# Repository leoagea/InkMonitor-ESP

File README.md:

# InkMonitor-ESP

InkMonitor-ESP is a lightweight temperature and humidity monitoring device built around an ESP microcontroller and an e‑paper display. This repository contains the hardware design files (KiCad) for the PCB and supporting assets.

## Highlights

- Low‑power ESP‑based monitoring platform
- E‑paper display for always‑on status with minimal power draw
- KiCad project files, BOM export, and board backups included

## Repository contents

- [PCB/](PCB/) — KiCad project, board/schematic, BOM, CAD assets, and exports
- [changelog.md](changelog.md) — project changes

## Hardware overview

The design targets a compact ESP‑based module (ESP32‑S3 class) paired with a temperature/humidity sensor and a small e‑paper display. The exact parts and footprints are defined in the KiCad files.

If you want to review or edit the design, open the KiCad project file:

- [PCB/InkMonitor-ESP.kicad_pro](PCB/InkMonitor-ESP.kicad_pro)

## Renders

1. Open the project file: [PCB/InkMonitor-ESP.kicad_pro](PCB/InkMonitor-ESP.kicad_pro).
2. Review the schematic: [PCB/InkMonitor-ESP.kicad_sch](PCB/InkMonitor-ESP.kicad_sch).
3. Review the PCB layout: [PCB/InkMonitor-ESP.kicad_pcb](PCB/InkMonitor-ESP.kicad_pcb).

## Firmware

WIP

## License

See [LICENSE](LICENSE).

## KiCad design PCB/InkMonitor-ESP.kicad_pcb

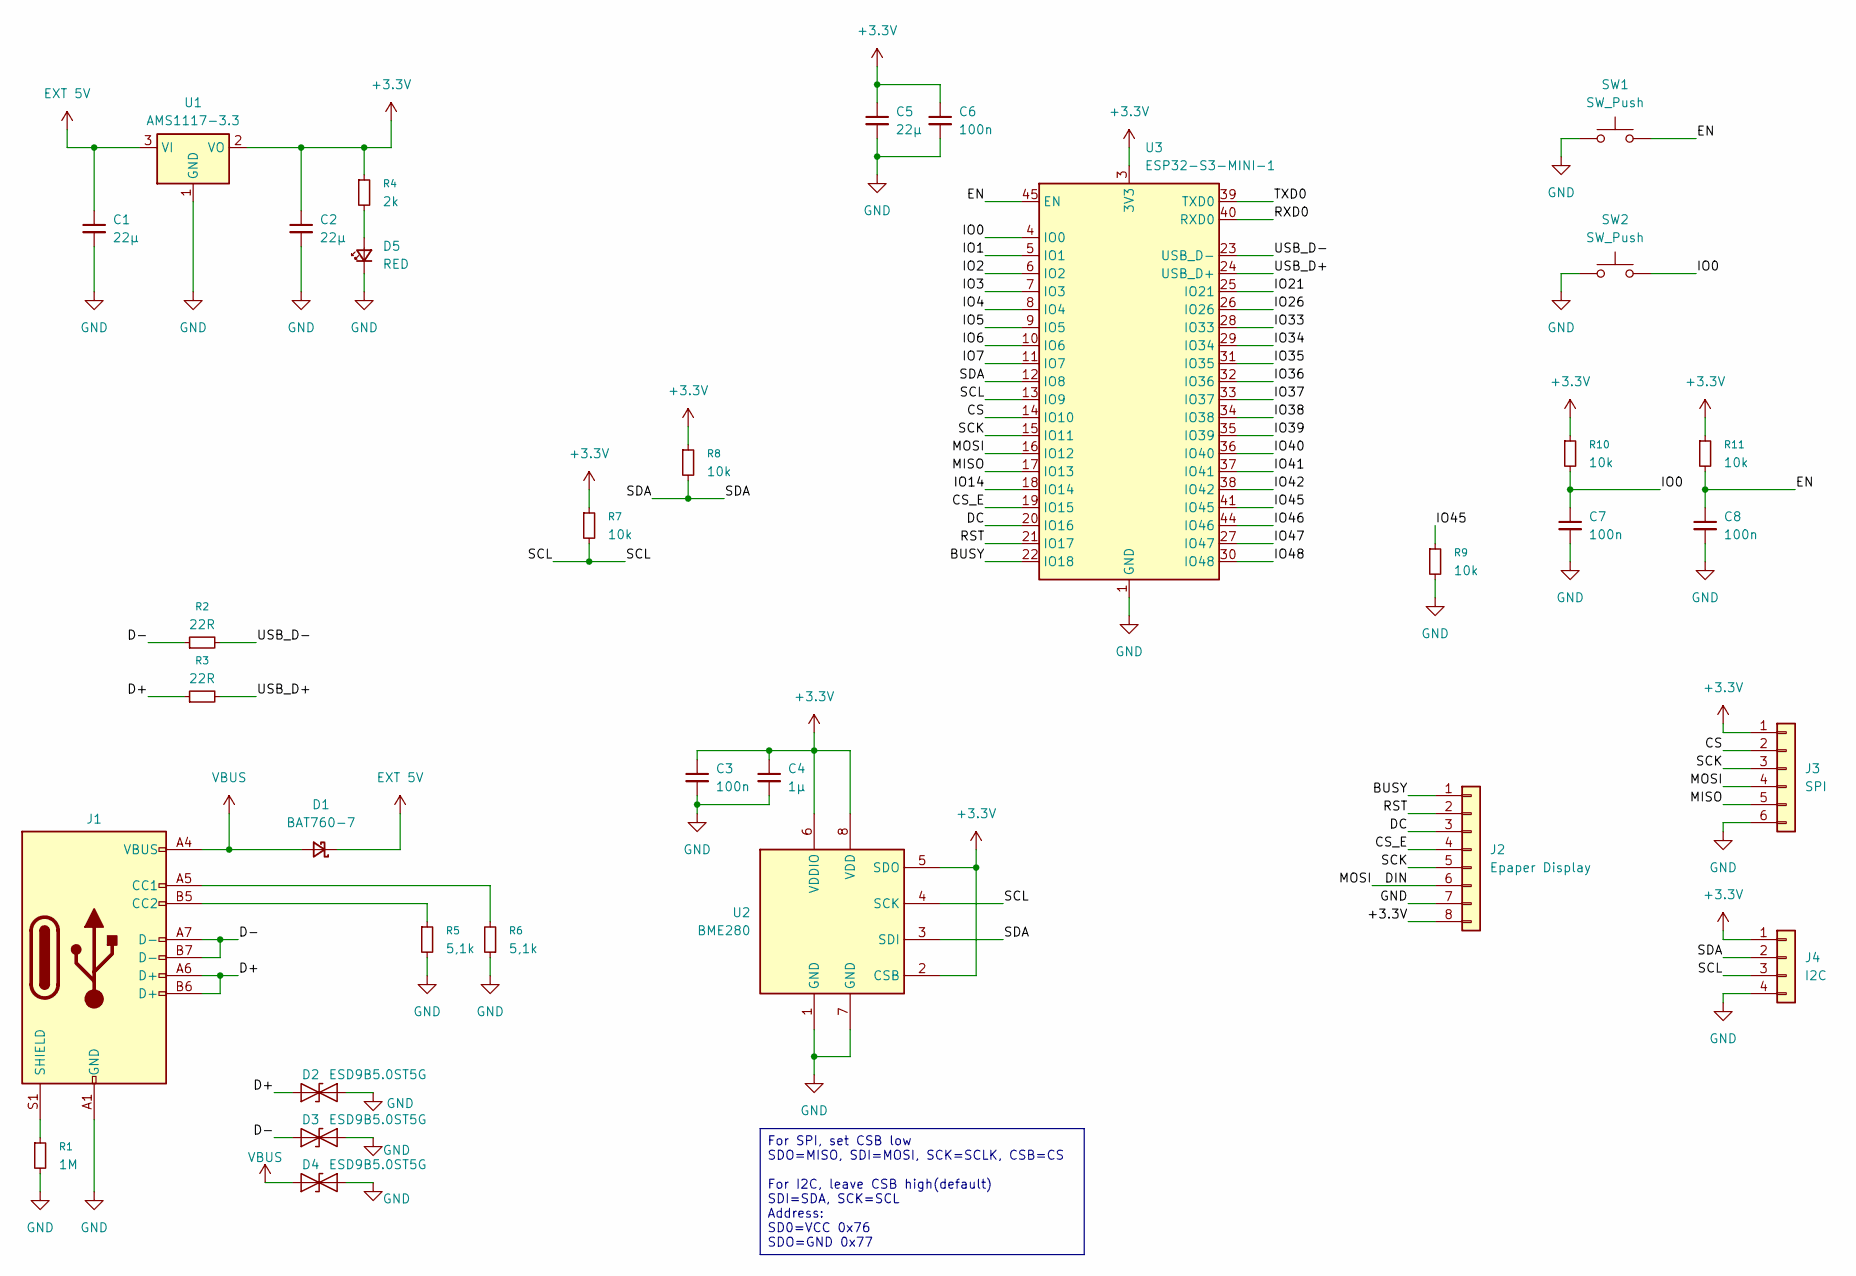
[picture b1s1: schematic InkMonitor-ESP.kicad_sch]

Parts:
C1, C2, C5: 22µ; C_0603_1608Metric_Pad1.08x0.95mm_HandSolder; LCSC C86295
C3, C6, C7, C8: 100n; C_0603_1608Metric_Pad1.08x0.95mm_HandSolder; LCSC C14663
C4: 1µ; C_0805_2012Metric_Pad1.18x1.45mm_HandSolder; LCSC C376929
D1: BAT760-7; D_SOD-323_HandSoldering; LCSC C27636120
D2, D3, D4: ESD9B5.0ST5G; D_SOD-923; LCSC C111566
D5: RED; LED_0603_1608Metric_Pad1.05x0.95mm_HandSolder; LCSC C19171390
J1: USB_C_Receptacle_USB2.0_14P; USB_C_Receptacle_GCT_USB4105-xx-A_16P_TopMnt_Horizontal; LCSC C2765186
J2: Epaper Display; JST_PH_B8B-PH-K_1x08_P2.00mm_Vertical
J3: SPI; JST_PH_B6B-PH-K_1x06_P2.00mm_Vertical
J4: I2C; JST_PH_B4B-PH-K_1x04_P2.00mm_Vertical
R1: 1M; R_0603_1608Metric_Pad0.98x0.95mm_HandSolder; LCSC C22935
R2, R3: 22R; R_0603_1608Metric_Pad0.98x0.95mm_HandSolder; LCSC C23345
R4: 2k; R_0603_1608Metric_Pad0.98x0.95mm_HandSolder; LCSC C2907137
R5, R6: 5,1k; R_0603_1608Metric_Pad0.98x0.95mm_HandSolder; LCSC C23186
R7, R8, R9, R10, R11: 10k; R_0603_1608Metric_Pad0.98x0.95mm_HandSolder; LCSC C2930027
SW1, SW2: SW_Push; SW_Push_1P1T_NO_CK_KMR2; LCSC C49393608
U1: AMS1117-3.3; SOT-223; LCSC C347222
U2: BME280; Bosch_LGA-8_2.5x2.5mm_P0.65mm_ClockwisePinNumbering
U3: ESP32-S3-MINI-1; ESP32-S2-MINI-1

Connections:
+3.3V: C2.1, C3.1, C4.1, C5.1, C6.1, J2.8, J3.1, J4.1, R4.1, R7.1, R8.1, R10.1, R11.1, U1.2 (VO), U2.2 (CSB), U2.5 (SDO), U2.6 (VDDIO), U2.8 (VDD), U3.3 (3V3); also elsewhere on the board
/BUSY: J2.1, U3.22 (IO18)
/CS: J3.2, U3.14 (IO10)
/CS_E: J2.4, U3.19 (IO15)
/D+: D2.2 (A2), J1.A6 (D+), J1.B6 (D+), R3.1
/D-: D3.2 (A2), J1.A7 (D-), J1.B7 (D-), R2.1
/DC: J2.3, U3.20 (IO16)
/DIN: J2.6, J3.4, U3.16 (IO12)
/EN: C8.1, R11.2, SW1.2, U3.45 (EN)
/IO0: C7.1, R10.2, SW2.2, U3.4 (IO0)
/IO1: U3.5 (IO1)
/IO2: U3.6 (IO2)
/IO3: U3.7 (IO3)
/IO4: U3.8 (IO4)
/IO5: U3.9 (IO5)
/IO6: U3.10 (IO6)
/IO7: U3.11 (IO7)
/IO14: U3.18 (IO14)
/IO21: U3.25 (IO21)
/IO26: U3.26 (IO26)
/IO33: U3.28 (IO33)
/IO34: U3.29 (IO34)
/IO35: U3.31 (IO35)
/IO36: U3.32 (IO36)
/IO37: U3.33 (IO37)
/IO38: U3.34 (IO38)
/IO39: U3.35 (IO39)
/IO40: U3.36 (IO40)
/IO41: U3.37 (IO41)
/IO42: U3.38 (IO42)
/IO45: R9.1, U3.41 (IO45)
/IO46: U3.44 (IO46)
/IO47: U3.27 (IO47)
/IO48: U3.30 (IO48)
/MISO: J3.5, U3.17 (IO13)
/RST: J2.2, U3.21 (IO17)
/RXD0: U3.40 (RXD0)
/SCK: J2.5, J3.3, U3.15 (IO11)
/SCL: J4.3, R7.2, U2.4 (SCK), U3.13 (IO9)
/SDA: J4.2, R8.2, U2.3 (SDI), U3.12 (IO8)
/TXD0: U3.39 (TXD0)
/USB_D+: R3.2, U3.24 (USB_D+)
/USB_D-: R2.2, U3.23 (USB_D-)
EXT 5V: C1.1, D1.1 (K), U1.3 (VI)
GND: C1.2, C2.2, C3.2, C4.2, C5.2, C6.2, C7.2, C8.2, D2.1 (A1), D3.1 (A1), D4.1 (A1), D5.1 (K), J1.A1 (GND), J1.A12 (GND), J1.B1 (GND), J1.B12 (GND), J2.7, J3.6, J4.4, R1.2, R5.2, R6.1, R9.2, SW1.1, SW2.1, U1.1 (GND), U2.1 (GND), U2.7 (GND), U3.1 (GND), U3.2 (GND), U3.42 (GND), U3.43 (GND), U3.46 (GND), U3.47 (GND), U3.48 (GND), U3.49 (GND), U3.50 (GND), U3.51 (GND), U3.52 (GND), U3.53 (GND), U3.54 (GND), U3.55 (GND), U3.56 (GND), U3.57 (GND), U3.58 (GND), U3.59 (GND), U3.60 (GND), U3.61 (GND), U3.62 (GND), U3.63 (GND), U3.64 (GND), U3.65 (GND); also elsewhere on the board
unnamed: D5.2 (A), R4.2
unnamed: J1.A5 (CC1), R6.2
unnamed: J1.B5 (CC2), R5.1
unnamed: J1.S1 (SHIELD), R1.1
VBUS: D1.2 (A), D4.2 (A2), J1.A4 (VBUS), J1.A9 (VBUS), J1.B4 (VBUS), J1.B9 (VBUS)

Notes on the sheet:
For SPI, set CSB low SDO=MISO, SDI=MOSI, SCK=SCLK, CSB=CS For I2C, leave CSB high(default) SDI=SDA, SCK=SCL Address: SD0=VCC 0x76 SDO=GND 0x77

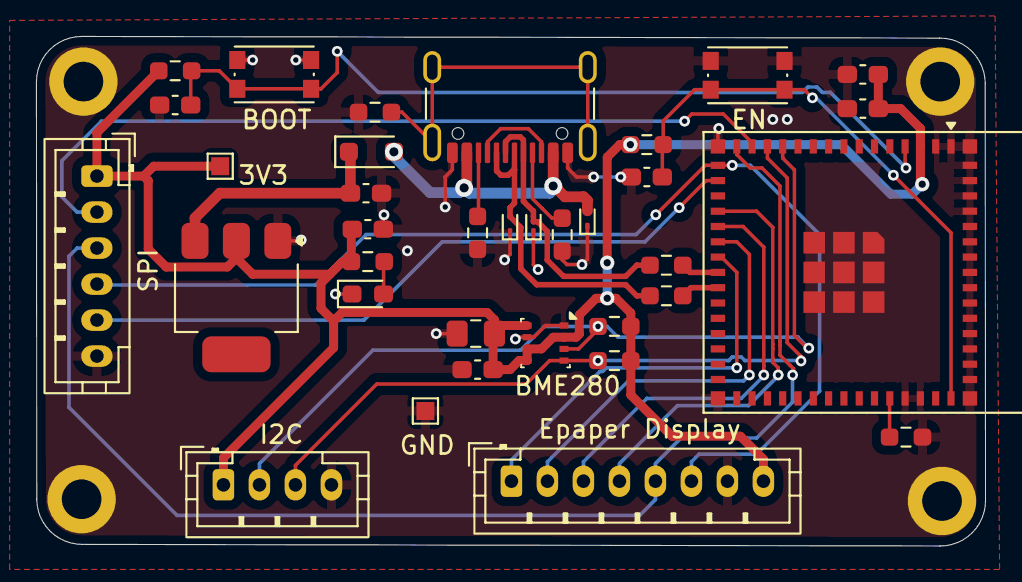
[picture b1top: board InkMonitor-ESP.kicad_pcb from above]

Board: 2 copper layers, 52.7 x 28.3 mm, 35 parts (0 on the bottom side), 25 nets.

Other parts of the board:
3V3: TestPoint_Pad_1.0x1.0mm
GND: TestPoint_Pad_1.0x1.0mm

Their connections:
+3.3V: 3V3.1; also elsewhere on the board
GND: GND.1; also elsewhere on the board

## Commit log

2026-02-17 V1, schematic + pcb
2026-02-17 Cad esp32-s3-mini
2026-02-17 V1 BOM
2026-02-17 chore: changelog.md
2026-02-17 V1 3D rendering
2026-02-17 chore: update readme
